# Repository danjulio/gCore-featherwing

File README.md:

Note: Check out my second version of [gCore](https://github.com/danjulio/gCore).

## gCore - A controller for portable GUI-based devices
gCore ("Gadget Core") is an ESP32 development board designed to mate with the [Adafruit TFT Featherwing](https://www.adafruit.com/product/3651) 480x320 pixel 3.5" TFT LCD display with resistive touch.  It contains a WROVER-B module, USB UART, true USB power-bath Li-Ion battery charger, a pair of ICR10440 batteries and a boost/buck 3.3V converter.  It is designed to support soft-power control and battery voltage/charge status monitoring.  A write-up exists on [hackaday.io](https://hackaday.io/project/170774-old-gcore-for-gui-based-gadgets).

gCore is released as open source hardware and supporting software under the GPLv3 license in hopes it will be helpful to others.  This repository contains two subdirectories.

1. hardware - contains eagle design files, gerber files, and documentation.
2. software - arduino library for power control, [LittlevGL](https://github.com/littlevgl) driver for Arduino and [FabGL](https://github.com/fdivitto/FabGL) port.

### gCore Operation
gCore is built around several components.

#### ESP32 Core
The ESP32 is a great micro-controller.  Powerful and inexpensive with a good amount of memory, WiFi, Bluetooth and full complement of peripherals.  Code can be written using Espressif's ESP IDF libraries and development environment or the ESP32 Arduino integration.  gCore uses a WROVER module because it also includes an external 8 MB PSRAM and up to 16 MB built-in flash enabling applications that require a lot of memory at the cost of two IO pins.

#### CP2102N USB UART
A Silicon Labs CP2102N USB UART provides access to the primary ESP32 serial port for programming and debug.  The RTS# and DTR# signals are interfaced to RESET# and IO0 in the traditional way so that external programming software can automatically upload new firmware.  While the ESP32 and other gCore devices are powered from its built-in power system, the CP2102 is powered by the USB port so that it does not add an additional load on the battery.  There is isolation circuitry to reduce sneak current paths between the two power domains.

The CP2102N CHRGEN and CHR0 signals are routed to the MCP73871 to allow for intelligent charge control based on the USB state.  These signals allow it to select a charge current of 0 mA when the USB Bus has been suspended (e.g. laptop sleeping), 100 mA when the USB Bus is running but the USB UART hasn't been enumerated yet or 500 mA when the USB Bus has been enumerated or gCore is connected to a dedicated USB Charger.  These features require the CP2102N be configured using software from Silicon Labs.  Please see the instructions in the Software/CP2102N subdirectory.

#### MCP73871 Load Sharing Charge Controller
A Microchip MCP73871 provides both the battery charging circuit and an intelligent power path that automatically routes power from USB, when available, to the Boost-Buck converter, augmenting it with power from the batteries when necessary.  This allows it to correctly identify when the batteries are charged (a problem with some other development boards that put the load on the same output that is charging the battery).  In addition the charge status signals are connected to a voltage divider network allowing the ESP32 to use an analog input to detect which of four states the charger is in.

* Charge Idle - Not charging.  Power either from USB or battery.
* Charging - Currently charging the battery
* Charge Done - Charging phase finished.  Power from USB.
* Fault - Charger detected a fault (see the spec sheet).

#### TPS63051 Boost-Buck Converter
A TI TPS63051 boost-buck converter provides gCore's 3.3V power supply at up to 500 mA.  Unlike many other development boards that only use a buck-converter (or inefficient linear regulator), it assures a valid 3.3V power supply even when the battery is depleted.  

#### Dual ICR10440 Li-Ion batteries
A pair of AAA-sized Li-Ion batteries allow for relatively thin enclosures.  The batteries are connected in parallel with each battery in series with a PTC to allow them to equalize during charge and discharge and protect from shorts.  They are capable of powering a device for a couple of hours of run-time.  Quality ICR10440 cells can be found on Amazon.  Since the charger can provide up to 450-500 mA when gCore is powered down always use two cells so the per-cell charge current doesn't exceed its recommended maximum.

A larger battery may also be used by connecting it to the terminals of one of the ICR10440 batteries.

**Update: See the note in the Hardware directory readme about issues with the dual battery system.** 

#### GPIO Utilization
| GPIO | Function | Notes |
|:----:|:--------:|:-----:|
| IO5  |  SPI SCK | SPI CLK for TFT, Touchscreen and Micro-SD |
| IO14 |   SD CS  | Micro-SD CS# on Adafruit TFT Featherwing |
| IO15 |  TFT CS  | TFT CS# on Adafruit TFT Featherwing |
| IO18 | SPI MOSI | SPI MOSI for TFT, Touchscreen and Micro-SD |
| IO19 | SPI MISO | SPI MISO for Touchscreen and Micro-SD |
| IO32 |   TS CS  | Touchscreen CS# on Adafruit TFT Featherwing |
| IO33 |  TFT DC  | TFT DC on Adafruit TFT Featherwing |
| IO34 | SNS_BTN  | ESP ADC1_CH6/Arduino A2 Button sense analog input |
| IO35 | SNS_BATT | ESP ADC1_CH7 Battery voltage sense analog input |
| IO36 | SNS_STAT | ESP ADC1_CH0/Arduino A4 charge stat sense analog input |

Note that both the SNS\_BTN and SNS\_STAT signals include jumper pads with a cuttable link to disconnect them from the analog input in case their functionality is not needed or the analog input needs to be used for another purpose.  See the schematic in the hardware sub-directory for more detail.

The two featherwing signals normally used to bring out the second ESP32 UART on its IO16 and IO17 pins are not connected because these pins are used internally by the WROVER module to support the PSRAM.

IO14 is available if no Micro-SD Card is inserted into the TFT Featherwing.

#### Available GPIO
The following GPIO are not connected and are available for application use.

| GPIO | Notes |
|:----:|:-----:|
| IO4  | A5 |
| IO12 | |
| IO13 | |
| IO21 | |
| IO22 | SCL |
| IO23 | SDA |
| IO25 | A1 |
| IO26 | A0 |
| IO27 | |
| IO39 | A3 |

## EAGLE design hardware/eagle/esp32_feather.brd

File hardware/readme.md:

## gCore Hardware Documentation

This directory contains the hardware design for gCore (Rev 2 design).

* documentation - BOM, schematic and board layout PDF renders, list of components to be loaded on the PCB.
* eagle - Eagle v7.7 design files
* gerber - Gerber files for PCB (not including stencil)
* stencil - Gerber files for top stencil

### Revision 2 Design Important Note
These files represent the second revision of the design.  To date I have only built the first revision and incorporated a few changes I found in Rev 2.  The changes were minor and I tested all of them with modifications (bodges) to the first revision. I am very confident that the second revision is correct and will work perfectly but in the spirit of full disclosure I'm letting you know.

#### Rev 2 PCB Top

#### Rev 2 PCB Bottom

### Hardware Notes

1. Turn the power switch located on the Adafruit TFT LCD featherwing to the ON position.  This allows the LCD backlight to be lit when 3.3V power comes on and also provides the ability to use the GPIO2 output on the STMPE610 touchscreen controller to turn it on and off under software control.

2. The CHREN and CHR0 signals between U1 (CP2102N) and U2 (MCP73871) are designed to work in conjunction with reconfiguring U1 via Simplicity Studio Xpress Configurator to support USB Charger detection.  Do not stuff R13 and R14 if you will not reconfigure U1.  This enables charging  at 500 mA.

2. Cut J3 between the pads if you do not want the power button sense circuitry attached to an analog input or you wish to attach it to a different analog input (connect a wire from the right pad to the desired analog input).

4. Cut J4 between the pads if you do not want the charge status sense circuitry attached to an analog input or you wish to attach it to a different analog input (connect a wire from the right pad to the desired analog input).

5. Two pins (J6-14, J6-15) on the featherwing expansion port are not connected.  On Sparkfun and Adafruit ESP32 featherwings these are connected to ESP32 GPIO 16 and 17.  However these pins are not available on the gCore's WROVER-B module.  They are used internally for the 8 MB PSRAM.

6. J1 is an optional jumper between the two USB data lines.  It should not be necessary and was included in case you ever attach a power supply to gCore that does not short the data lines.  The CP2102N will enable charging because it thinks the bus is not enumerated and there is no charger attached.  But be sure to remove the jumper before connecting to a computer!

### Battery Notes
After using a pair of gCore prototypes for some time I found that one unit would no longer keep the batteries balanced and they would slowly discharge.  The other unit works fine.  Experimentation described in more detail on the hackaday.io project page was unsuccessful in explaining why so now I must add the caveat that using the dual ICR10440 battery solution may not work.  It's easy, however, to use a single battery, connected to one pair of battery terminals, with its PTC bypassed, and the AAA battery holders removed or not installed.

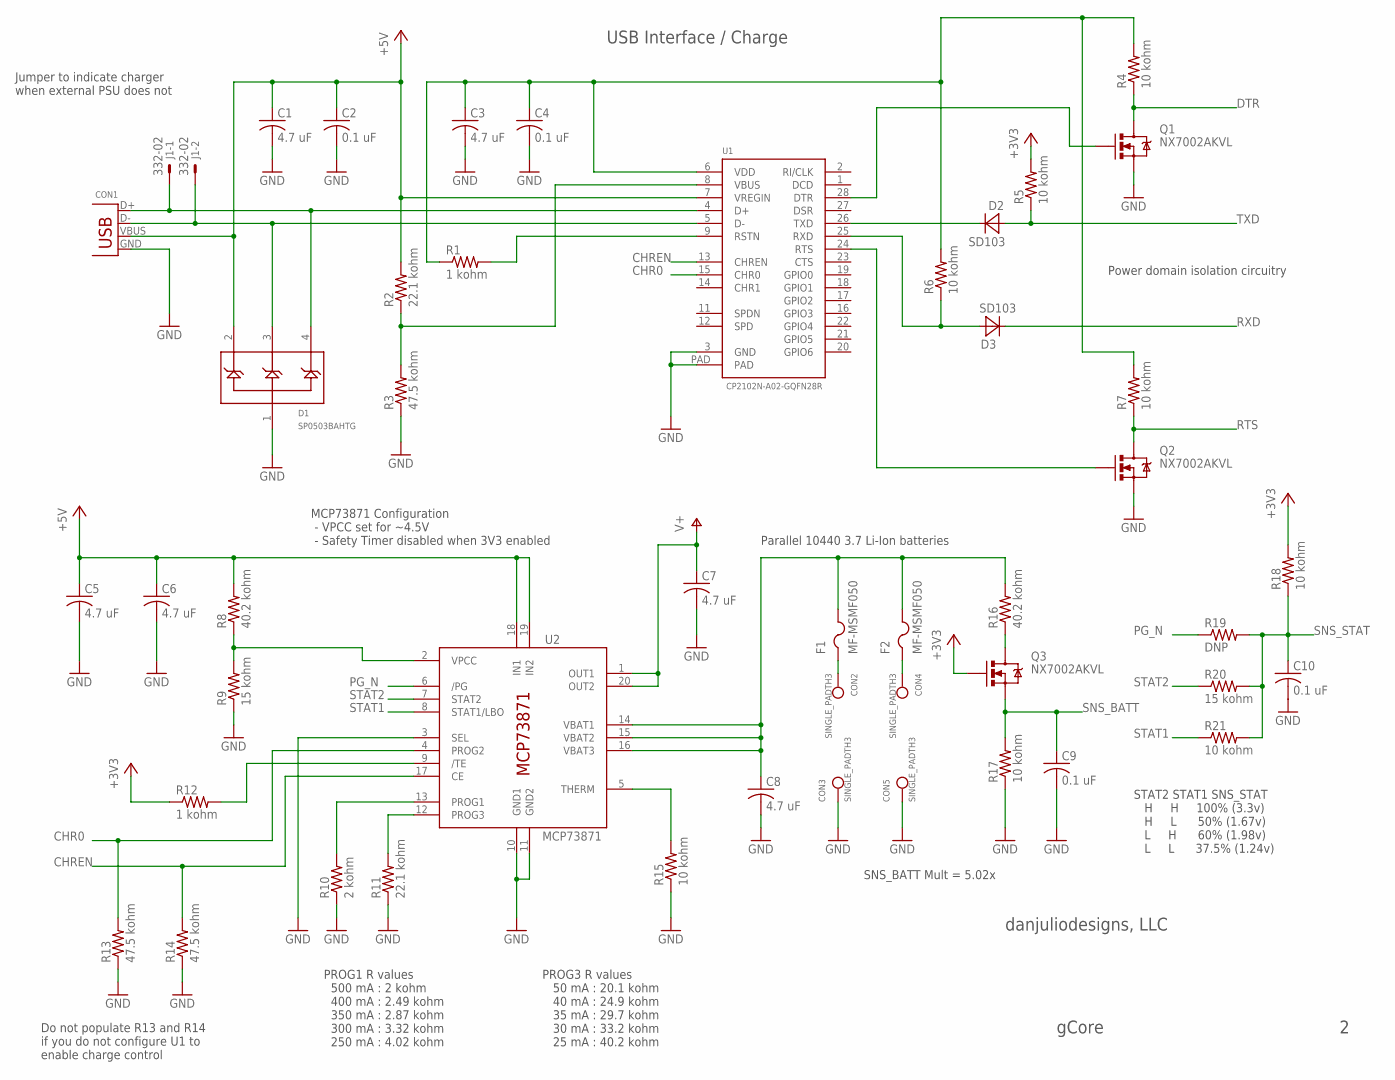
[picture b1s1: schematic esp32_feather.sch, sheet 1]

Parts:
C1, C3, C5, C6, C7, C8: 4.7 uF; C0603
C2, C4, C9, C10: 0.1 uF; C0603
CON1: USBMICROB; USB_MICROB_SMT
CON2, CON3, CON4, CON5: SINGLE_PADTH3; SINGLE_PAD_POWER
D1: SP0503BAHTG; SOT143
D2, D3: SD103; SOD123
F1, F2: MF-MSMF050; 1812
J1: 332-02
Q1, Q2, Q3: NX7002AKVL; SOT23-3
R1, R12: 1 kohm; R0603
R2, R11: 22.1 kohm; R0603
R3, R13, R14: 47.5 kohm; R0603
R4, R5, R6, R7, R15, R17, R18, R21: 10 kohm; R0603
R8, R16: 40.2 kohm; R0603
R9, R20: 15 kohm; R0603
R10: 2 kohm; R0603
R19: DNP; R0603
U1: CP2102N-A02-GQFN28R; QFN28
U2: MCP73871; QFN20

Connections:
+3V3: Q3.1 (G), R5.2, R12.1, R18.2; also elsewhere on the board
+5V: C1.1, C2.1, C5.1, C6.1, CON1.VBUS, D1.2 (C1), R2.2, R8.2, U1.7 (VREGIN), U2.18 (IN1), U2.19 (IN2); also elsewhere on the board
CHR0: R13.2, U1.15 (CHR0), U2.4 (PROG2)
CHREN: R14.2, U1.13 (CHREN), U2.17 (CE)
DTR: Q1.3 (D), R4.1; also elsewhere on the board
GND: C1.2, C2.2, C3.2, C4.2, C5.2, C6.2, C7.2, C8.2, C9.2, C10.2, CON1.GND, CON3.P$1, CON5.P$1, D1.1 (GND), Q1.2 (S), Q2.2 (S), R3.1, R9.1, R10.1, R11.1, R13.1, R14.1, R15.1, R17.1, U1.3 (GND), U1.PAD, U2.3 (SEL), U2.10 (GND1), U2.11 (GND2); also elsewhere on the board
unnamed: CON1.D+, D1.4 (C3), J1.1, U1.4 (D+)
unnamed: CON1.D-, D1.3 (C2), J1.2, U1.5 (D-)
unnamed: R15.2, U2.5 (THERM)
unnamed: C8.1, F1.2, F2.2, R16.2, U2.14 (VBAT1), U2.15 (VBAT2), U2.16 (VBAT3)
unnamed: R1.2, U1.9 (RSTN)
unnamed: Q1.1 (G), U1.28 (DTR)
unnamed: R8.1, R9.2, U2.2 (VPCC)
unnamed: R2.1, R3.2, U1.8 (VBUS)
unnamed: D2.C, U1.26 (TXD)
unnamed: D3.A, R6.1, U1.25 (RXD)
unnamed: Q2.1 (G), U1.24 (RTS)
unnamed: R10.2, U2.13 (PROG1)
unnamed: R11.2, U2.12 (PROG3)
unnamed: CON2.P$1, F1.1
unnamed: CON4.P$1, F2.1
unnamed: R12.2, U2.9 (/TE)
unnamed: Q3.3 (D), R16.1
PG_N: R19.1, U2.6 (/PG)
RTS: Q2.3 (D), R7.1; also elsewhere on the board
RXD: D3.C; also elsewhere on the board
SNS_BATT: C9.1, Q3.2 (S), R17.2; also elsewhere on the board
SNS_STAT: C10.1, R18.1, R19.2, R20.2, R21.2; also elsewhere on the board
STAT1: R21.1, U2.8 (STAT1/LBO)
STAT2: R20.1, U2.7 (STAT2)
TXD: D2.A, R5.1; also elsewhere on the board
V+: C7.1, U2.1 (OUT1), U2.20 (OUT2); also elsewhere on the board
VDD: C3.1, C4.1, R1.1, R4.2, R6.2, R7.2, U1.6 (VDD)

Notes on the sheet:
Parallel 10440 3.7 Li-Ion batteries
USB Interface / Charge
danjuliodesigns, LLC
gCore
PROG3 R values 50 mA : 20.1 kohm 40 mA : 24.9 kohm 35 mA : 29.7 kohm 30 mA : 33.2 kohm 25 mA : 40.2 kohm
PROG1 R values 500 mA : 2 kohm 400 mA : 2.49 kohm 350 mA : 2.87 kohm 300 mA : 3.32 kohm 250 mA : 4.02 kohm
MCP73871 Configuration - VPCC set for ~4.5V - Safety Timer disabled when 3V3 enabled
Power domain isolation circuitry
SNS_BATT Mult = 5.02x
STAT2 STAT1 SNS_STAT H H 100% (3.3v) H L 50% (1.67v) L H 60% (1.98v) L L 37.5% (1.24v)
Jumper to indicate charger when external PSU does not
Do not populate R13 and R14 if you do not configure U1 to enable charge control

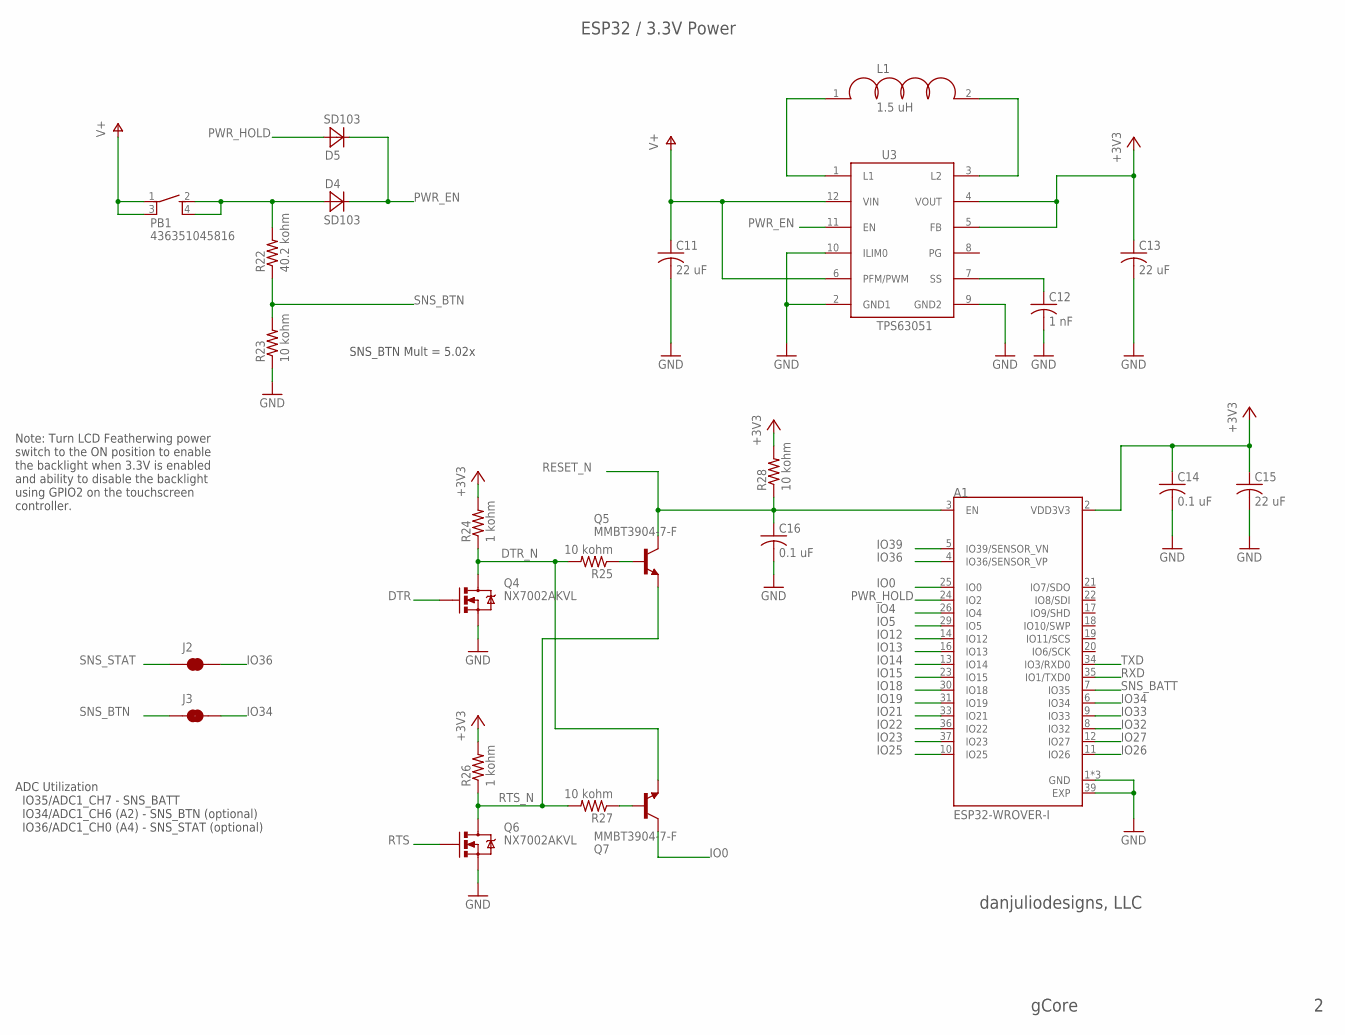
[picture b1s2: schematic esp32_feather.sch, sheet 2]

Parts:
A1: ESP32-WROVER-I; XCVR_ESP32-WROVER-I
C11, C13, C15: 22 uF; C0603
C12: 1 nF; C0603
C14, C16: 0.1 uF; C0603
D4, D5: SD103; SOD123
J2, J3: SJ_WIRED; SJ_2B_ADA
L1: 1.5 uH; L1008
PB1: 436351045816; WURTH_WS_TASU_TACT
Q4, Q6: NX7002AKVL; SOT23-3
Q5, Q7: MMBT3904-7-F; SOT23-BEC
R22: 40.2 kohm; R0603
R23, R25, R27, R28: 10 kohm; R0603
R24, R26: 1 kohm; R0603
U3: TPS63051; HOTROD_QFN12

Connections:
+3V3: A1.2 (VDD3V3), C13.1, C14.1, C15.1, R24.2, R26.2, R28.2, U3.4 (VOUT), U3.5 (FB); also elsewhere on the board
DTR: Q4.1 (G); also elsewhere on the board
DTR_N: Q4.3 (D), Q7.E, R24.1, R25.2
GND: A1.1 (GND), A1.15 (GND), A1.38 (GND), A1.39 (EXP), C11.2, C12.2, C13.2, C14.2, C15.2, C16.2, Q4.2 (S), Q6.2 (S), R23.1, U3.2 (GND1), U3.9 (GND2), U3.10 (ILIM0); also elsewhere on the board
IO0: A1.25 (IO0), Q7.C
IO4: A1.26 (IO4); also elsewhere on the board
IO5: A1.29 (IO5); also elsewhere on the board
IO12: A1.14 (IO12); also elsewhere on the board
IO13: A1.16 (IO13); also elsewhere on the board
IO14: A1.13 (IO14); also elsewhere on the board
IO15: A1.23 (IO15); also elsewhere on the board
IO18: A1.30 (IO18); also elsewhere on the board
IO19: A1.31 (IO19); also elsewhere on the board
IO21: A1.33 (IO21); also elsewhere on the board
IO22: A1.36 (IO22); also elsewhere on the board
IO23: A1.37 (IO23); also elsewhere on the board
IO25: A1.10 (IO25); also elsewhere on the board
IO26: A1.11 (IO26); also elsewhere on the board
IO27: A1.12 (IO27); also elsewhere on the board
IO32: A1.8 (IO32); also elsewhere on the board
IO33: A1.9 (IO33); also elsewhere on the board
IO34: A1.6 (IO34), J3.2; also elsewhere on the board
IO36: A1.4 (IO36/SENSOR_VP), J2.2; also elsewhere on the board
IO39: A1.5 (IO39/SENSOR_VN); also elsewhere on the board
unnamed: L1.1, U3.1 (L1)
unnamed: L1.2, U3.3 (L2)
unnamed: C12.1, U3.7 (SS)
unnamed: D4.A, PB1.2 (3), PB1.4, R22.2
unnamed: Q5.B, R25.1
unnamed: Q7.B, R27.1
PWR_EN: D4.C, D5.C, U3.11 (EN)
PWR_HOLD: A1.24 (IO2), D5.A
RESET_N: A1.3 (EN), C16.1, Q5.C, R28.1; also elsewhere on the board
RTS: Q6.1 (G); also elsewhere on the board
RTS_N: Q5.E, Q6.3 (D), R26.1, R27.2
RXD: A1.35 (IO1/TXD0); also elsewhere on the board
SNS_BATT: A1.7 (IO35); also elsewhere on the board
SNS_BTN: J3.1, R22.1, R23.2
SNS_STAT: J2.1; also elsewhere on the board
TXD: A1.34 (IO3/RXD0); also elsewhere on the board
V+: C11.1, PB1.1, PB1.3 (2), U3.6 (PFM/PWM), U3.12 (VIN); also elsewhere on the board

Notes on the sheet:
ESP32 / 3.3V Power
danjuliodesigns, LLC
gCore
SNS_BTN Mult = 5.02x
Note: Turn LCD Featherwing power switch to the ON position to enable the backlight when 3.3V is enabled and ability to disable the backlight using GPIO2 on the touchscreen controller.
ADC Utilization IO35/ADC1_CH7 - SNS_BATT IO34/ADC1_CH6 (A2) - SNS_BTN (optional) IO36/ADC1_CH0 (A4) - SNS_STAT (optional)

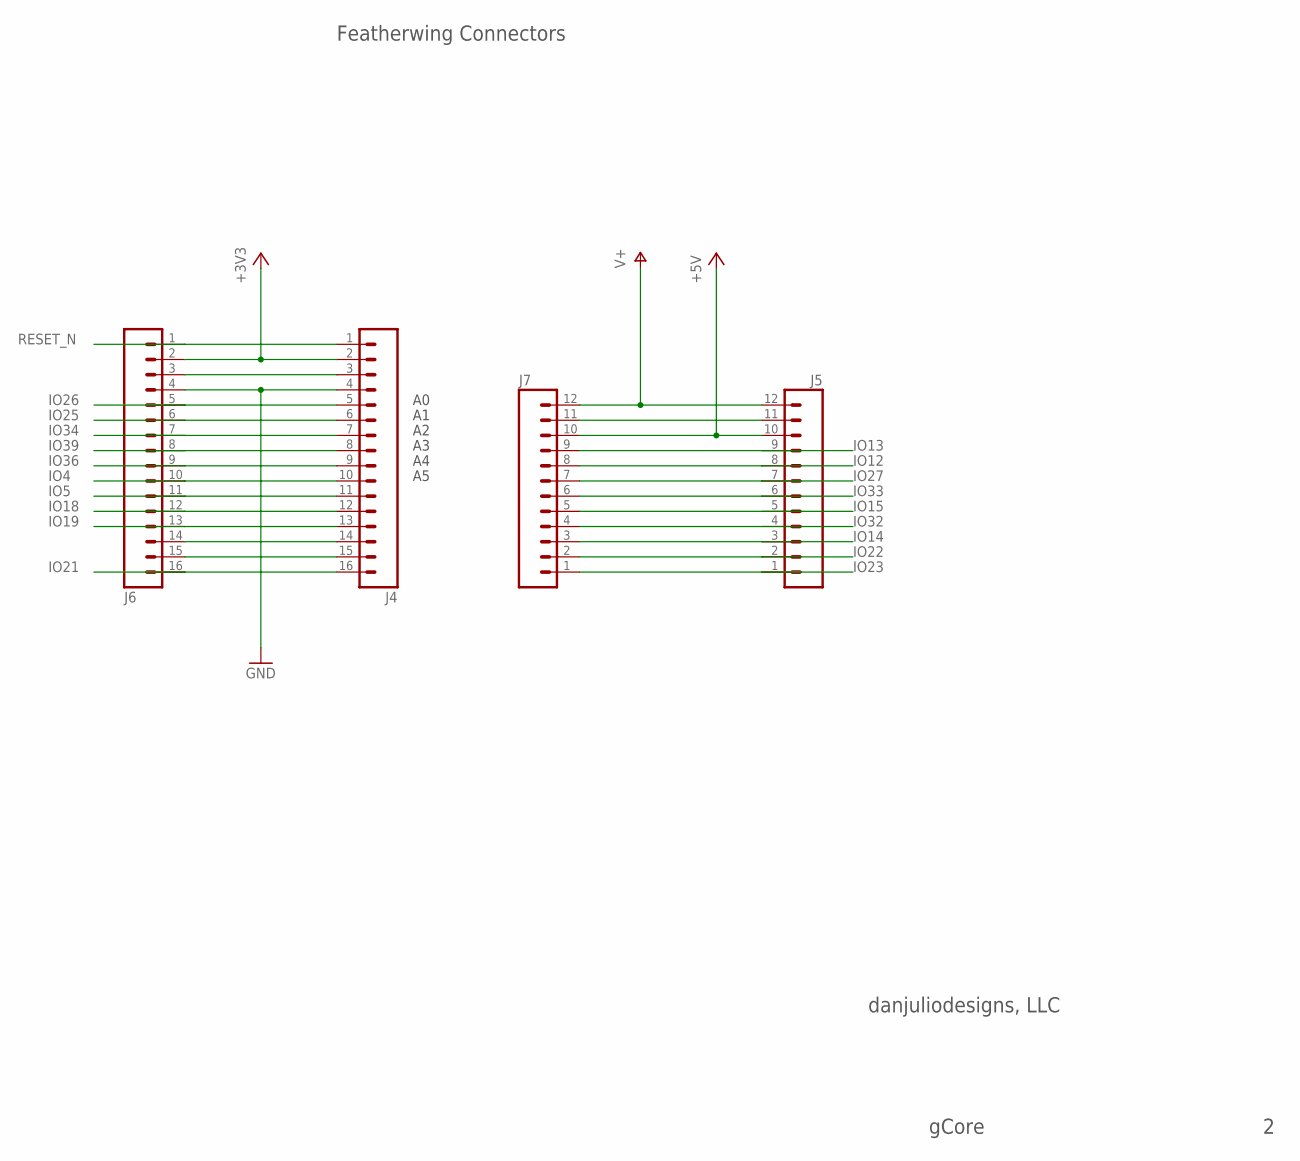
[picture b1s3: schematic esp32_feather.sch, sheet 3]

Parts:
J4, J6: M16PTH; 1X16
J5, J7: M12PTH; 1X12

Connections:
+3V3: J4.2, J6.2; also elsewhere on the board
+5V: J5.10, J7.10; also elsewhere on the board
FTHR_EN: J5.11, J7.11
GND: J4.4, J6.4; also elsewhere on the board
IO4: J4.10, J6.10; also elsewhere on the board
IO5: J4.11, J6.11; also elsewhere on the board
IO12: J5.8, J7.8; also elsewhere on the board
IO13: J5.9, J7.9; also elsewhere on the board
IO14: J5.3, J7.3; also elsewhere on the board
IO15: J5.5, J7.5; also elsewhere on the board
IO18: J4.12, J6.12; also elsewhere on the board
IO19: J4.13, J6.13; also elsewhere on the board
IO21: J4.16, J6.16; also elsewhere on the board
IO22: J5.2, J7.2; also elsewhere on the board
IO23: J5.1, J7.1; also elsewhere on the board
IO25: J4.6, J6.6; also elsewhere on the board
IO26: J4.5, J6.5; also elsewhere on the board
IO27: J5.7, J7.7; also elsewhere on the board
IO32: J5.4, J7.4; also elsewhere on the board
IO33: J5.6, J7.6; also elsewhere on the board
IO34: J4.7, J6.7; also elsewhere on the board
IO36: J4.9, J6.9; also elsewhere on the board
IO39: J4.8, J6.8; also elsewhere on the board
unnamed: J4.3, J6.3
unnamed: J4.14, J6.14
unnamed: J4.15, J6.15
RESET_N: J4.1, J6.1; also elsewhere on the board
V+: J5.12, J7.12; also elsewhere on the board

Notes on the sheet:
Featherwing Connectors
danjuliodesigns, LLC
gCore

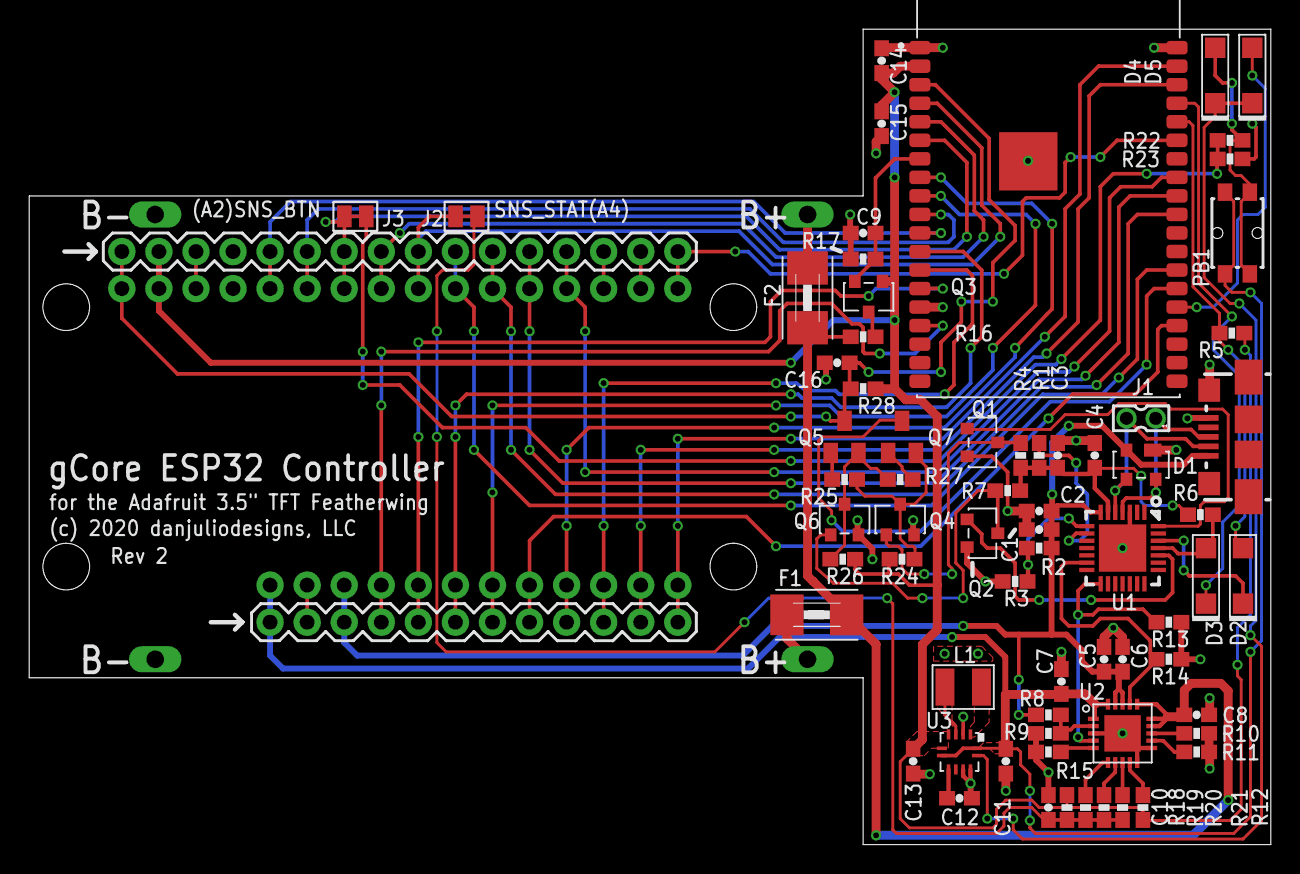
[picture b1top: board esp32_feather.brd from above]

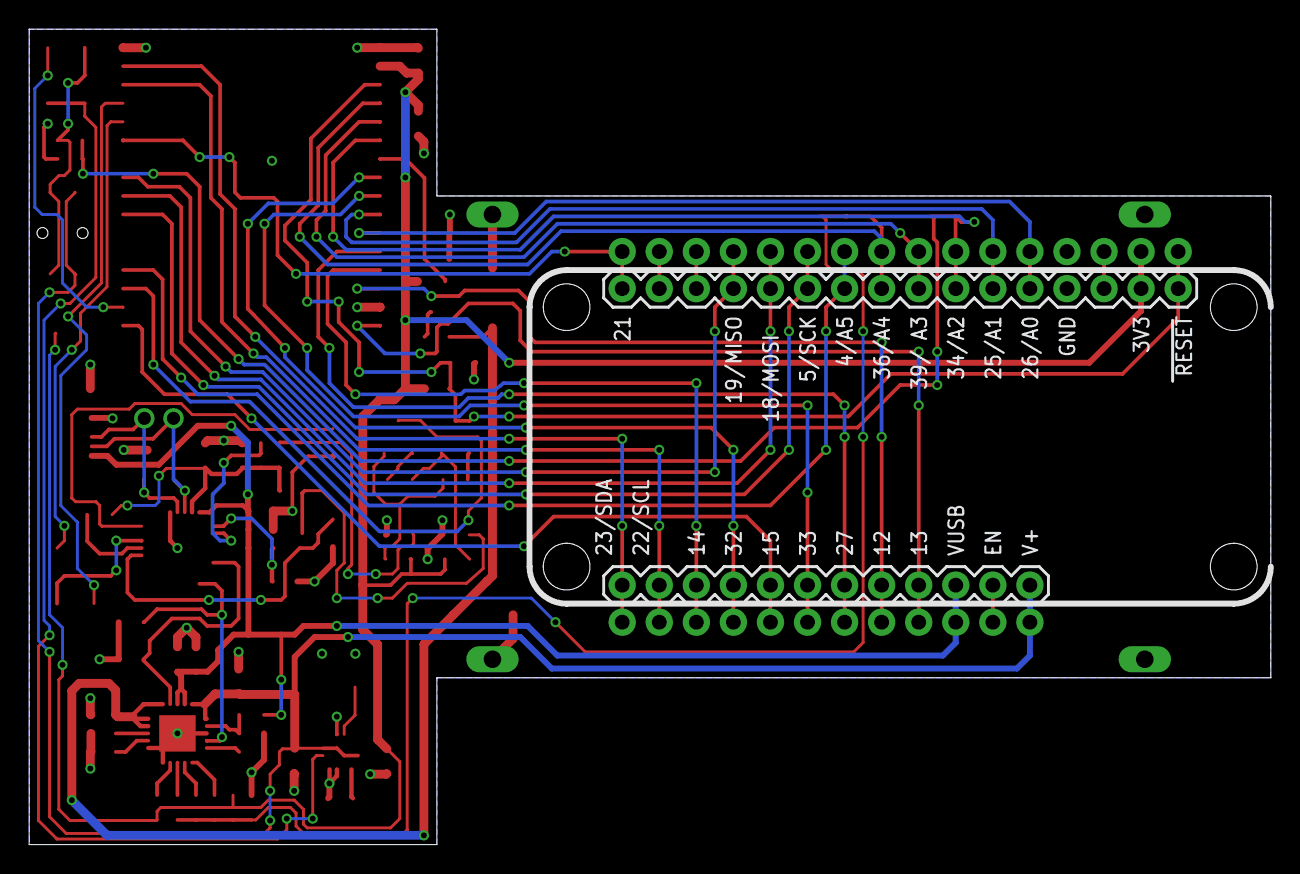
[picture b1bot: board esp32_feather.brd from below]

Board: 2 copper layers, 85.1 x 55.9 mm, 76 parts (2 on the bottom side), 69 nets.

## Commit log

2020-04-21 Initial checkin
2020-04-26 Fixed typos and slightly improved readme text.
2020-04-26 Fixed typo
2020-05-23 Update readme files
    Added unused GPIO, link to hackaday.io project and new info about issues with battery balancing.
2020-05-23 correct project name
2020-05-23 fixed typo in comment
2020-05-23 init variable
2022-06-27 Fixed bug in touchscreen driver
2022-06-27 Added hex_calculator demo
2022-12-03 Added link to new gCore

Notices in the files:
hardware/eagle/esp32_feather.brd:
(c) 2020 danjuliodesigns, LLC
parts and their libraries:
SparkFun-Connectors: Licensing: Creative Commons ShareAlike 4.0 International - https://creativecommons.org/licenses/by-sa/4.0
